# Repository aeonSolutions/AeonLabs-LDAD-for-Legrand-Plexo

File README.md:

[Main Catalogue](https://github.com/aeonSolutions/PCB-Prototyping-Catalogue) >> 
[Construction Industry](https://github.com/aeonSolutions/PCB-Prototyping-Catalogue/tree/main/Construction%20Industry)  >>  [
Building & Indoor](https://github.com/aeonSolutions/PCB-Prototyping-Catalogue/tree/main/Construction%20Industry/Building%20%26%20Indoor)

<p align="right">
 <a href="https://github-com.translate.goog/aeonSolutions/PCB-Prototyping-Catalogue/tree/main?_x_tr_sl=en&_x_tr_tl=pt&_x_tr_hl=en&_x_tr_pto=wapp">Change Language</a> <br>
Last update: 30-11-2023
</p>

# AeonLabs LDAD for Legrand Plexo
 #LDAD PCB for a direct fit on [Legrand Plexo](https://www.legrand.com/ecatalogue/RESIDENTIAL-BUILDINGS-AND-HOTEL-EQUIPMENT/weatherproof-wiring-accessories-and-other-installation-equipment:5/weatherproof-wiring-accessories-and-boxes:1/plexo-boxes-ip-55-ik-07-with-direct-entry-membrane-glands-650-c:12/square-boxes:2/65-x-) Junction Box with 65x65x40xmm.

Features WIFI, BLE & Bluetooth 5.x connectivity and can connect up to 10 sensors. This PCB is powered with any 220V AC line. This new LDAD for Legrand , has already built in CANBUS Network connectivity compatible with ISO 11898-2 for data transmission (and receive) up to 1Mbit/s. Ready to deploy using [Home Assistant](https://www.home-assistant.io/) tools! 

The perfect #PCB for managing construction site works since early construction stages, while, for instance, concreting structural elements. Later on can be left and integrated with any home automation system for active structural and environmental monitoring.

Simple and compatible with existing tools and technologies. Can't get better than this !!! 

*Don't forget to LIKE , SHARE and subscribe the free whatsApp group* and if you liked this PCB consider buying me a cup of coffee. Links below.

### Status
  Waiting for first batch from factory to be tested.

If you already tested this PCB send me a message. Thank you

## Revisions
- revision 1.1
   - added 220V AC Fuse 
  
## Download options
Download this repository if you need the KiCad Files or, download the Gerber files in the release section of this repository

## Liked it ? Get a Free PCB for yourself
Send me your Device or hardware and i will design a custom PCB for it. Free of charge. Contact-me on WhatsApp or email for more info. 

## Q&A WhatsApp Group
If you have any Questions or simply  like this kind of projects and want to stay updated with the latest research ideas and prototypes during the day and week, join the WhatsApp Group
[A.I. Things](https://chat.whatsapp.com/FkNC7u83kuy2QRA5sqjBVg)

## Fully assembled PCB
Alternatively, and if you do not want to build a PCB by yourself and like to buy one:

The price starts at 30eur plus postage fees.
(I will also deliver the assembled PCB with all the components in place at a fair aditonal cost).

#### Be supportive of my dedication and work towards technology education and buy me a coffee. Link below.

________________________________________________________________________________________________________________
## [Go back to main catalogue page](https://github.com/aeonSolutions/PCB-Prototyping-Catalogue)
________________________________________________________________________________________________________________

## PCB Parts list
- DC2DC converter HX4002B x2 : https://s.click.aliexpress.com/e/_Ak7IPx
- Capacitor 100nF SMD 1206 : https://s.click.aliexpress.com/e/_AVdmzr
- Capacitor 2.2uF SMD 1206 : https://s.click.aliexpress.com/e/_AVdmzr
- Resistor SMD 1206 330R x3 : https://s.click.aliexpress.com/e/_A7OXrR
- ESP32 WROOM32 x1 : https://s.click.aliexpress.com/e/_AF7N6l
- KF350 Screw pitch 3.5mm Straight 3 Pin pcb terminal block : https://s.click.aliexpress.com/e/_AChDnp

- This PCB connects with the DS18b20 Temperature sensor : https://s.click.aliexpress.com/e/_AWDAMr 

## PCB Enclosure
The enclosure for this PCB can be bought online by searching for [Legrand Plexo](https://www.legrand.com/ecatalogue/RESIDENTIAL-BUILDINGS-AND-HOTEL-EQUIPMENT/weatherproof-wiring-accessories-and-other-installation-equipment:5/weatherproof-wiring-accessories-and-boxes:1/plexo-boxes-ip-55-ik-07-with-direct-entry-membrane-glands-650-c:12/square-boxes:2/65-x-) .

## Firmware Download 
one can use the PCB in the repository [AeonLabs-MCU-Burner-USB-to-UART-TTL](https://github.com/aeonSolutions/AeonLabs-MCU-Burner-USB-to-UART-TTL) to program the ESP32 WROOM32 MCU on this PCB.

<br>

## Author

You can get in touch with me on my LinkedIn Profile:

#### Miguel Tomas

You can also follow my GitHub Profile to stay updated about my latest projects: 

<br>

### Be supportive of my dedication and work towards technology education and buy me a cup of coffee
The PCB Desgin Files i provide here for anyone to use are free. If you like this Smart Device or use it, please consider buying me a cup of coffee, a slice of pizza or a book to help me study, eat and think new PCB design files.

<br />

### Make a donation on Paypal
Make a donation on paypal and get a TAX refund*.

<br>

### Support all these open hardware projects and become a patreon  
Liked any of my PCB KiCad Designs? Help and Support my open work to all by becomming a LDAD Patreon.
In return I will give a free PCB design in KiCad to all patreon supporters. To learn more go to patreon.com. Link below.

#

### License

Before proceeding to download any of AeonLabs software solutions for open-source development and/or PCB hardware electronics solutions for open-hardware development make sure you are choosing the right license for your project. See [AeonLabs Solutions for Open Hardware & Source Development](https://github.com/aeonSolutions/PCB-Prototyping-Catalogue/wiki/AeonLabs-Solutions-for-Open-Hardware-&-Source-Development) for more information.

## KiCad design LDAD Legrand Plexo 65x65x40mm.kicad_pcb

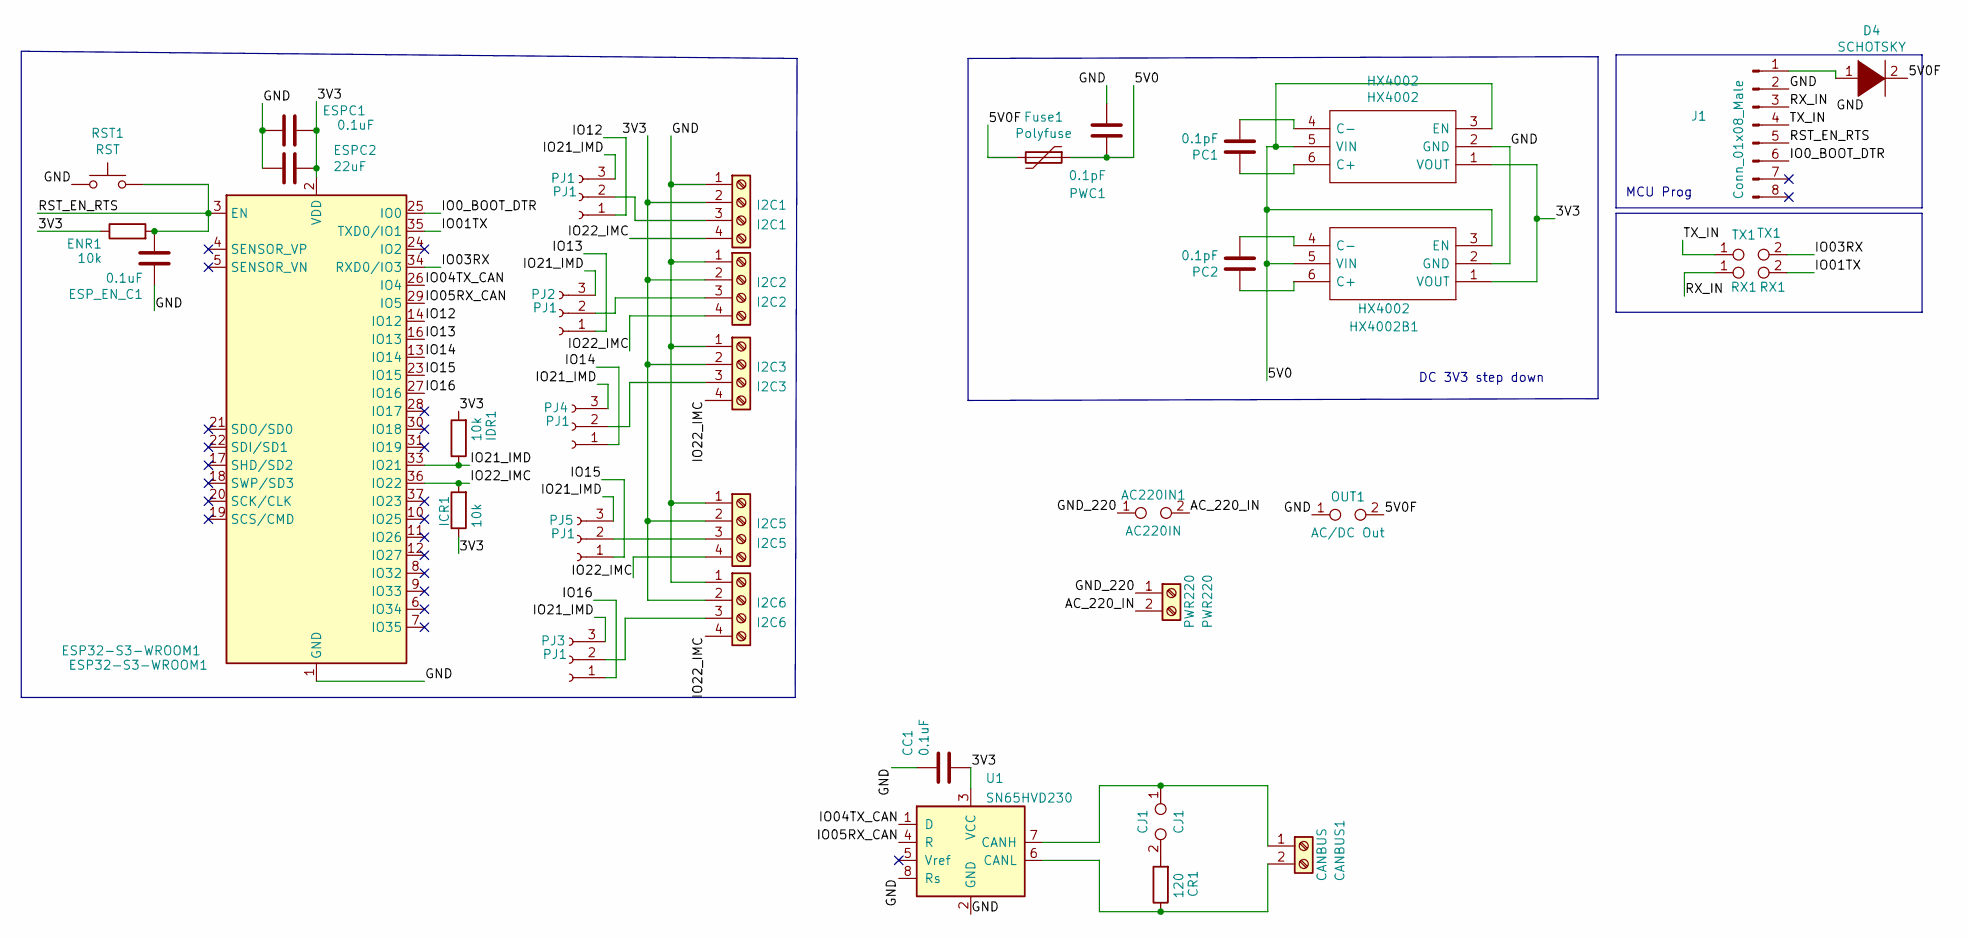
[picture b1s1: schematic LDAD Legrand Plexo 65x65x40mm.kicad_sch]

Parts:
AC220IN1: AC220IN; TestPoint_2Pads_Pitch3.81mm_Drill1.3mm
CANBUS1: CANBUS; TerminalBlock_bornier-2_P5.08mm
CC1: 0.1uF; C_1206_3216Metric_Pad1.33x1.80mm_HandSolder
CJ1: CJ1; TestPoint_2Pads_Pitch2.54mm_Drill0.8mm
CR1: 120; R_1206_3216Metric_Pad1.30x1.75mm_HandSolder
D4: SCHOTSKY; D_1210_3225Metric_Pad1.42x2.65mm_HandSolder
ENR1: 10k; R_1206_3216Metric_Pad1.30x1.75mm_HandSolder
ESP32-S3-WROOM1: ESP32-S3-WROOM1; ESP32-WROOM-32
ESPC1: 0.1uF; C_1206_3216Metric_Pad1.33x1.80mm_HandSolder
ESPC2: 22uF; C_1206_3216Metric_Pad1.33x1.80mm_HandSolder
ESP_EN_C1: 0.1uF; C_1206_3216Metric_Pad1.33x1.80mm_HandSolder
Fuse1: Polyfuse; Fuse_1206_3216Metric_Pad1.42x1.75mm_HandSolder
HX4002, HX4002B1: HX4002; HX4002 SOT95 P280X125-6N; Manufacturer_Part_Number HX4002
I2C1: I2C1; TerminalBlock_4Ucon_1x04_P3.50mm_Vertical
I2C2: I2C2; TerminalBlock_4Ucon_1x04_P3.50mm_Vertical
I2C3: I2C3; TerminalBlock_4Ucon_1x04_P3.50mm_Vertical
I2C5: I2C5; TerminalBlock_4Ucon_1x04_P3.50mm_Vertical
I2C6: I2C6; TerminalBlock_4Ucon_1x04_P3.50mm_Vertical
ICR1: 10k; R_1206_3216Metric_Pad1.30x1.75mm_HandSolder
IDR1: 10k; R_1206_3216Metric_Pad1.30x1.75mm_HandSolder
J1: Conn_01x08_Male; SOIC_clipProgSmall
OUT1: AC/DC Out; TestPoint_2Pads_Pitch2.54mm_Drill0.8mm
PC1, PC2: 0.1pF; C_1206_3216Metric_Pad1.33x1.80mm_HandSolder
PJ1, PJ2, PJ3, PJ4, PJ5: PJ1; TestPoint_3Pads_Pitch2.54mm_Drill0.8mm
PWC1: 0.1pF; C_1206_3216Metric_Pad1.33x1.80mm_HandSolder
PWR220: PWR220; TerminalBlock_bornier-2_P5.08mm
RST1: RST; SW_Push_SPST_NO_Alps_SKRK AliExpress
RX1: RX1; TestPoint_Pad_Bridge_1.0x1.0mm
TX1: TX1; TestPoint_Pad_Bridge_1.0x1.0mm
U1: SN65HVD230; SOIC-8_3.9x4.9mm_P1.27mm

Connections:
/3V3: CC1.2, ENR1.1, ESP32-S3-WROOM1.2 (VDD), ESPC1.1, ESPC2.1, HX4002.1 (VOUT), HX4002B1.1 (VOUT), I2C1.2, I2C2.2, I2C3.2, I2C5.2, I2C6.2, ICR1.1, IDR1.2, U1.3 (VCC)
/5V0: Fuse1.1, HX4002.3 (EN), HX4002.5 (VIN), HX4002B1.3 (EN), HX4002B1.5 (VIN), PWC1.1
/5V0F: D4.2 (A), Fuse1.2, OUT1.2
/AC_220_IN: AC220IN1.2, PWR220.2
/GND: CC1.1, ESP32-S3-WROOM1.1 (GND), ESP32-S3-WROOM1.15 (GND), ESP32-S3-WROOM1.38 (GND), ESP32-S3-WROOM1.39 (GND), ESPC1.2, ESPC2.2, ESP_EN_C1.1, HX4002.2 (GND), HX4002B1.2 (GND), I2C1.1, I2C2.1, I2C3.1, I2C5.1, I2C6.1, J1.2, OUT1.1, PWC1.2, RST1.1, U1.2 (GND), U1.8 (Rs)
/GND_220: AC220IN1.1, PWR220.1
/IO0_BOOT_DTR: ESP32-S3-WROOM1.25 (IO0), J1.6
/IO01TX: ESP32-S3-WROOM1.35 (TXD0/IO1), RX1.2
/IO03RX: ESP32-S3-WROOM1.34 (RXD0/IO3), TX1.2
/IO04TX_CAN: ESP32-S3-WROOM1.26 (IO4), U1.1 (D)
/IO05RX_CAN: ESP32-S3-WROOM1.29 (IO5), U1.4 (R)
/IO12: ESP32-S3-WROOM1.14 (IO12), PJ1.1
/IO13: ESP32-S3-WROOM1.16 (IO13), PJ2.1
/IO14: ESP32-S3-WROOM1.13 (IO14), PJ4.1
/IO15: ESP32-S3-WROOM1.23 (IO15), PJ5.1
/IO16: ESP32-S3-WROOM1.27 (IO16), PJ3.1
/IO21_IMD: ESP32-S3-WROOM1.33 (IO21), IDR1.1, PJ1.3, PJ2.3, PJ3.3, PJ4.3, PJ5.3
/IO22_IMC: ESP32-S3-WROOM1.36 (IO22), I2C1.4, I2C2.4, I2C3.4, I2C5.4, I2C6.4, ICR1.2
/RST_EN_RTS: ENR1.2, ESP32-S3-WROOM1.3 (EN), ESP_EN_C1.2, J1.5, RST1.2
/RX_IN: J1.3, RX1.1
/TX_IN: J1.4, TX1.1
unnamed: CANBUS1.1, CJ1.1, U1.7 (CANH)
unnamed: CANBUS1.2, CR1.1, U1.6 (CANL)
unnamed: CJ1.2, CR1.2
unnamed: D4.1 (K), J1.1
unnamed: HX4002.4 (C-), PC1.2
unnamed: HX4002.6 (C+), PC1.1
unnamed: HX4002B1.4 (C-), PC2.2
unnamed: HX4002B1.6 (C+), PC2.1
unnamed: I2C1.3, PJ1.2
unnamed: I2C2.3, PJ2.2
unnamed: I2C3.3, PJ4.2
unnamed: I2C5.3, PJ5.2
unnamed: I2C6.3, PJ3.2

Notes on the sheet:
DC 3V3 step down
MCU Prog

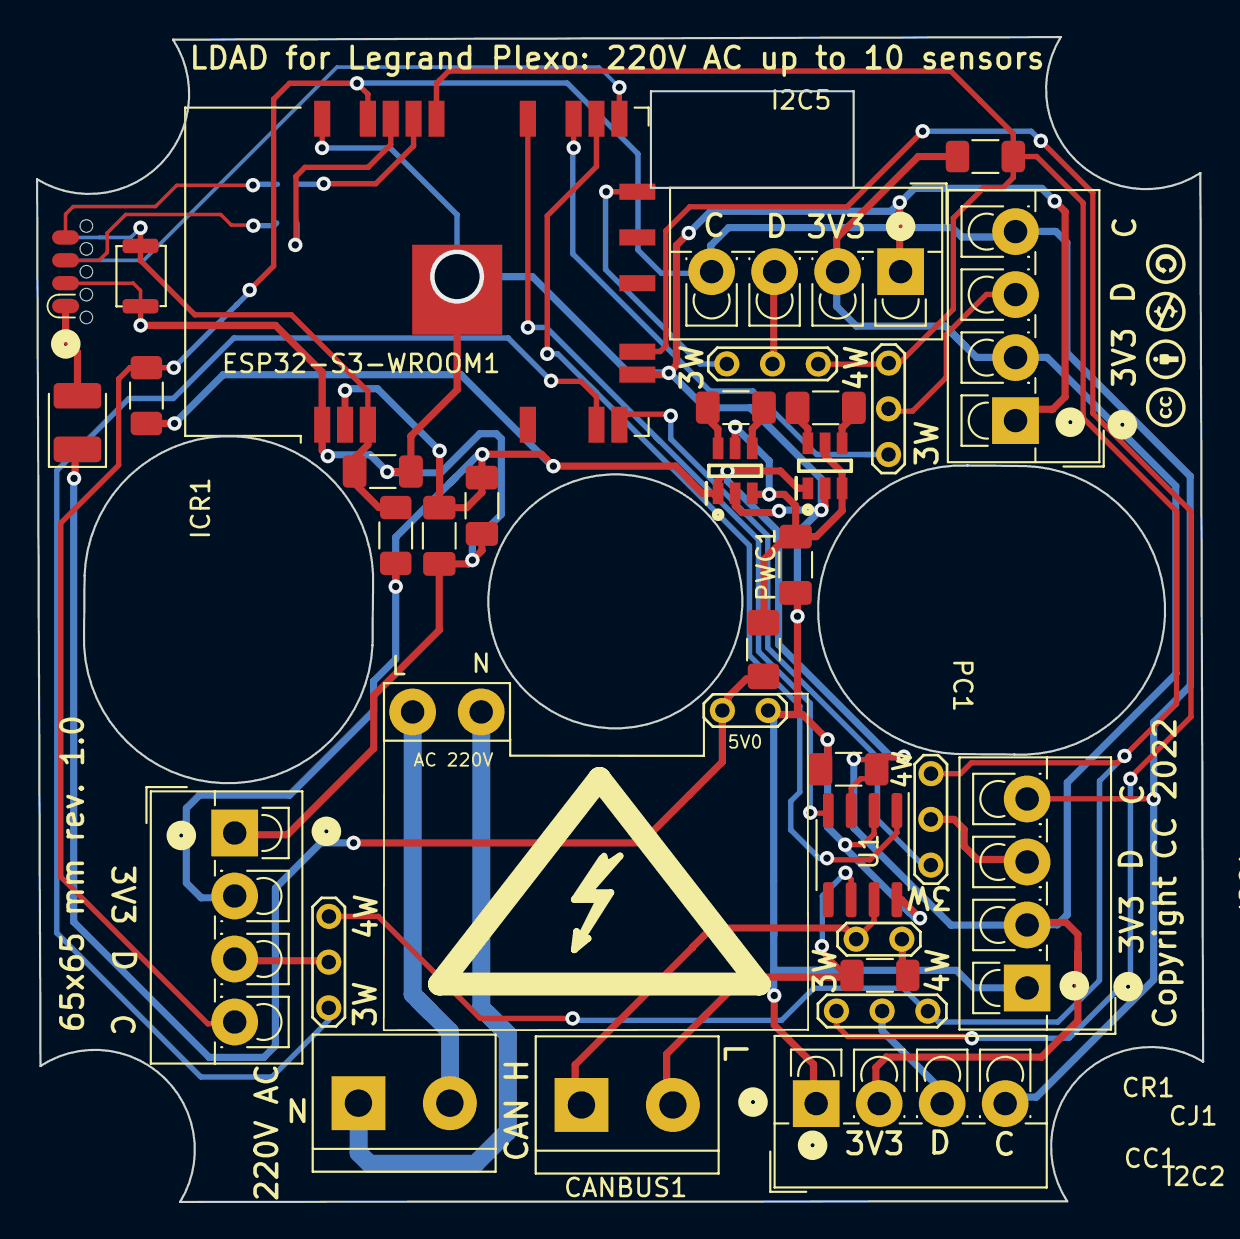
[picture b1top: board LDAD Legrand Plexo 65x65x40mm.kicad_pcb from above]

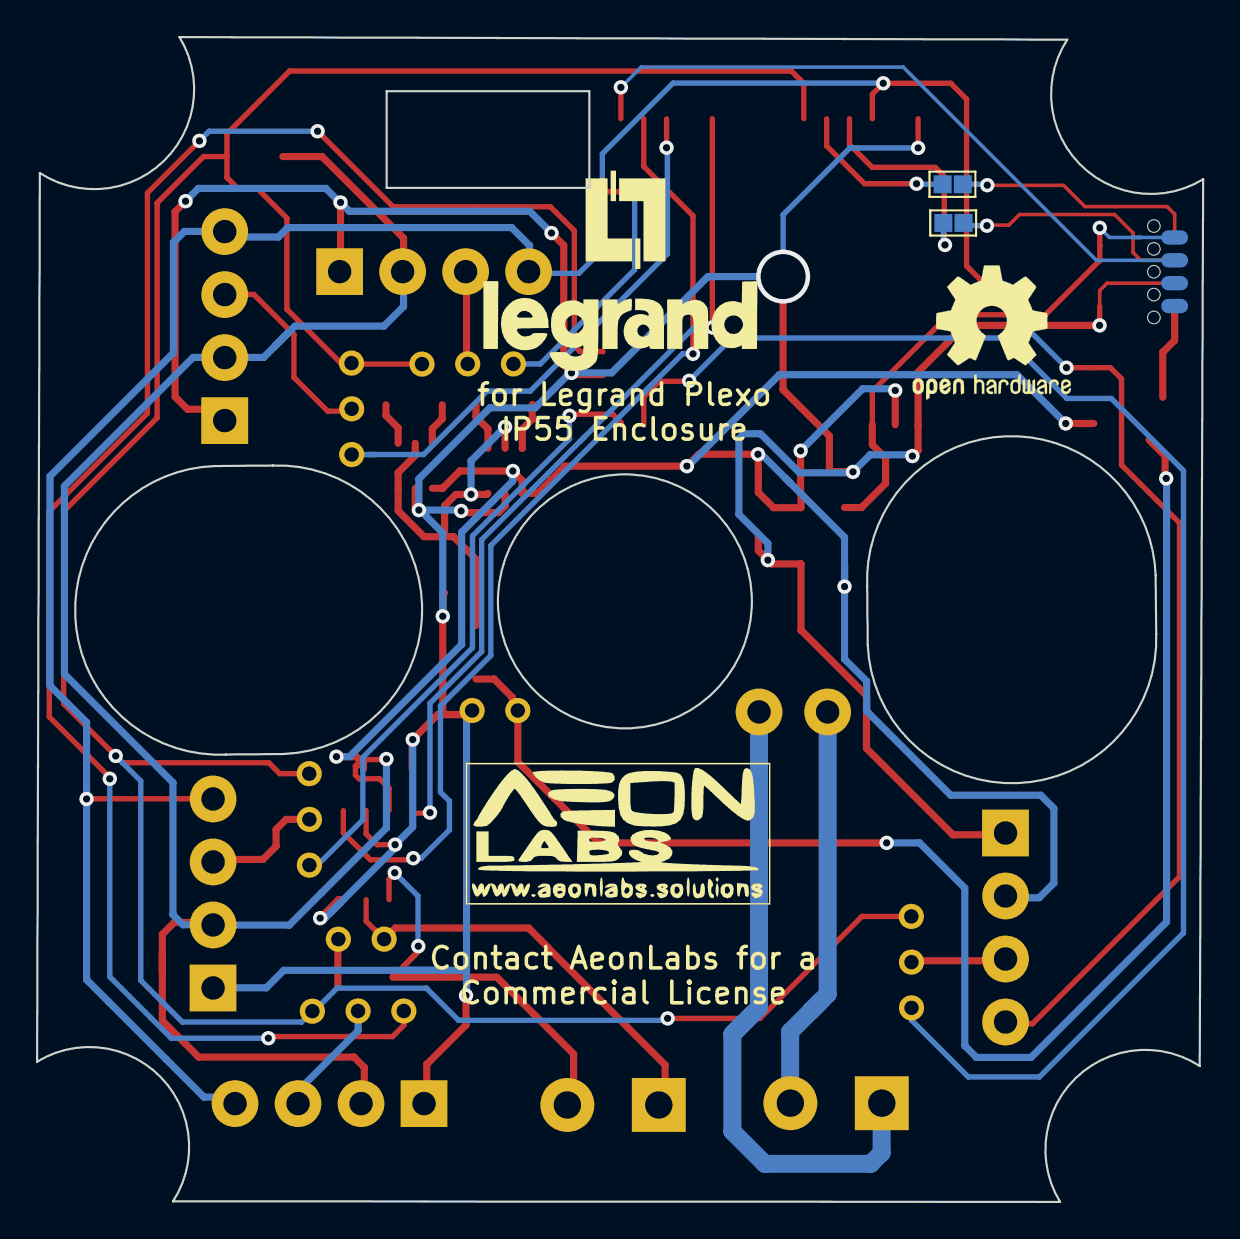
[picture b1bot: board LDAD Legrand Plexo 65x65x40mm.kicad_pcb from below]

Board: 2 copper layers, 64.8 x 64.7 mm, 36 parts (2 on the bottom side), 34 nets.

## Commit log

2022-06-05 revision 1.0
2022-06-06 Add files via upload
    updated

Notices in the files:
LDAD Legrand Plexo 65x65x40mm.kicad_pcb:
Copyright CC 2022
